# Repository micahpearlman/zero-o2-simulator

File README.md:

## Zero O2 Simulator

An O2 or lambda simulator is used to send a simulated oxygen/lambda sensor signal to an engine ECU running in closed loop mode. O2 sensors generate voltages between 0.9V (rich) and 0.1V (lean).  A properly running simulator will generate an oscillation of 1-2Hz at 0.6V to 0.3V (though check your specific application).

This uses an ATTiny85 as the signal generator (using DDS, see: http://cho-yaba.punyu.jp/?p=1663).  Where most O2 simulators in the past used a 555 timer the ATTiny85 gives the advantage of being fully programmable.

## Status

May 2 2015 - This is still early proof of concept version.  The hardware design will work and the current software emits a sine wave signal.  The signal will need to be tuned for your specific application and will require modification.  

## TODO

* Modify circuit to accept external rich <--> lean control via a digital pot. (currently need to reprogram the microcontroller).
* Create a surface mount component version.

## License

BSD License (free to use it, copy it, etc)

## References

  ATTiny signal generation using DDS: http://cho-yaba.punyu.jp/?p=1663
  555 O2 Simulator Project: http://www.bobblick.com/techref/projects/o2sensor/o2sim/o2sim.html

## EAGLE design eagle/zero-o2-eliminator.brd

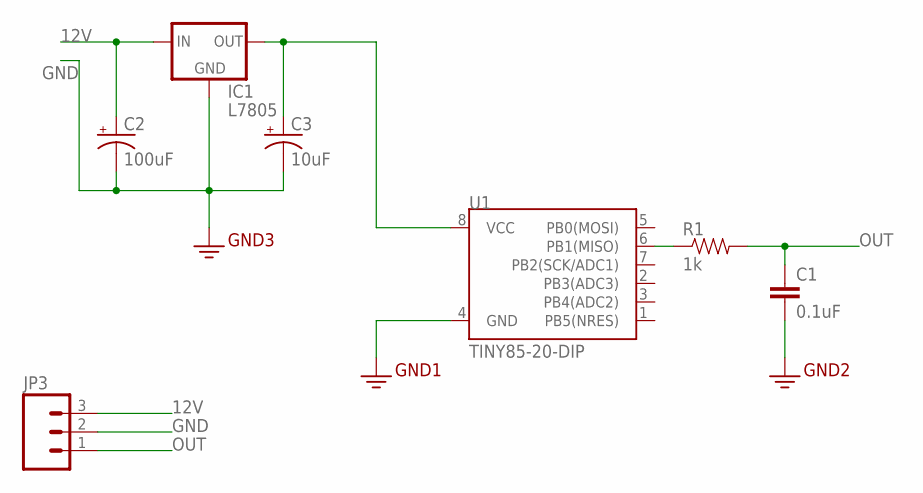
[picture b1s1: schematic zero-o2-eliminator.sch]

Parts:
C1: 0.1uF; CAP-PTH-SMALL-KIT
C2: 100uF; CPOL-RADIAL-10UF-25V-KIT
C3: 10uF; CPOL-RADIAL-10UF-25V-KIT
IC1: L7805; 78XXL
JP3: M03SCREW; SCREWTERMINAL-3.5MM-3
R1: 1k; AXIAL-0.1EZ
U1: TINY85-20-DIP; DIP08

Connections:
12V: C2.1 (+), IC1.IN, JP3.3
GND: C1.2, C2.2 (-), C3.2 (-), IC1.GND, JP3.2, U1.4 (GND)
unnamed: R1.P$1 (1), U1.6 (PB1(MISO))
unnamed: C3.1 (+), IC1.OUT, U1.8 (VCC)
OUT: C1.1, JP3.1, R1.P$2 (2)

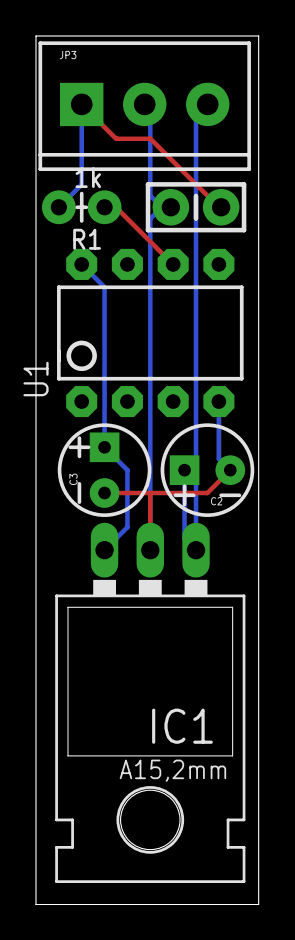
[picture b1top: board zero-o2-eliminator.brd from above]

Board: 2 copper layers, 12.4 x 48.2 mm, 7 parts (0 on the bottom side), 5 nets.

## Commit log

2015-04-19 initial commit. (working arduino function generator)
2015-04-19 added reading from table
2015-04-19 added eagle
2015-04-19 created initial board
2015-05-02 latest
2015-05-02 added readme
2015-05-02 added doc with schematic and board images
2015-05-02 updated readme with schematic image
2015-05-02 updated readme with more images

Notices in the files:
parts and their libraries:
SparkFun-Capacitors: Licensing: Creative Commons ShareAlike 4.0 International - https://creativecommons.org/licenses/by-sa/4.0
